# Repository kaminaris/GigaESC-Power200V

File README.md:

# GigaPower200V

Compact 50 × 20 mm non-isolated power-supply module for the modular GigaESC platform, intended for the 200 V version. Provides 12 V, 5 V and 3.3 V rails through a separate output connector.

## Board views

## Hardware

- TL494 PWM controller, IR2181 gate driver and TL431 reference circuitry.
- Two AP63356DV buck regulators for the lower-voltage rails.
- Two 2×10 connectors separating input and output connections.
- Common ground between input and outputs; no galvanic isolation.

## Connector summary

| Connector | Pins | Signal |
|---|---|---|
| J1 input | 3, 5 | VIN |
| J1 input | 17–20 | GND |
| J2 output | 3, 4 | 12 V |
| J2 output | 7, 8 | 5 V |
| J2 output | 11, 12 | 3.3 V |
| J2 output | 1, 2, 5, 6, 9, 10, 13–16, 19, 20 | GND |

Remaining connector pins are unconnected in the schematic. Use the current schematic as the authoritative pinout.

## Project

Open `GigaPower200V.kicad_pro` in KiCad 10. Schematic and layout are in `GigaPower200V.kicad_sch` and `GigaPower200V.kicad_pcb`. Local libraries are included; keep the connector STEP model alongside the project.

The project name describes the intended voltage class, not a measured operating limit. Input range, output loading and thermal performance require hardware validation. The inherited `LM5164_DESIGN.md` describes an earlier design and is not documentation for the current TL494 implementation.

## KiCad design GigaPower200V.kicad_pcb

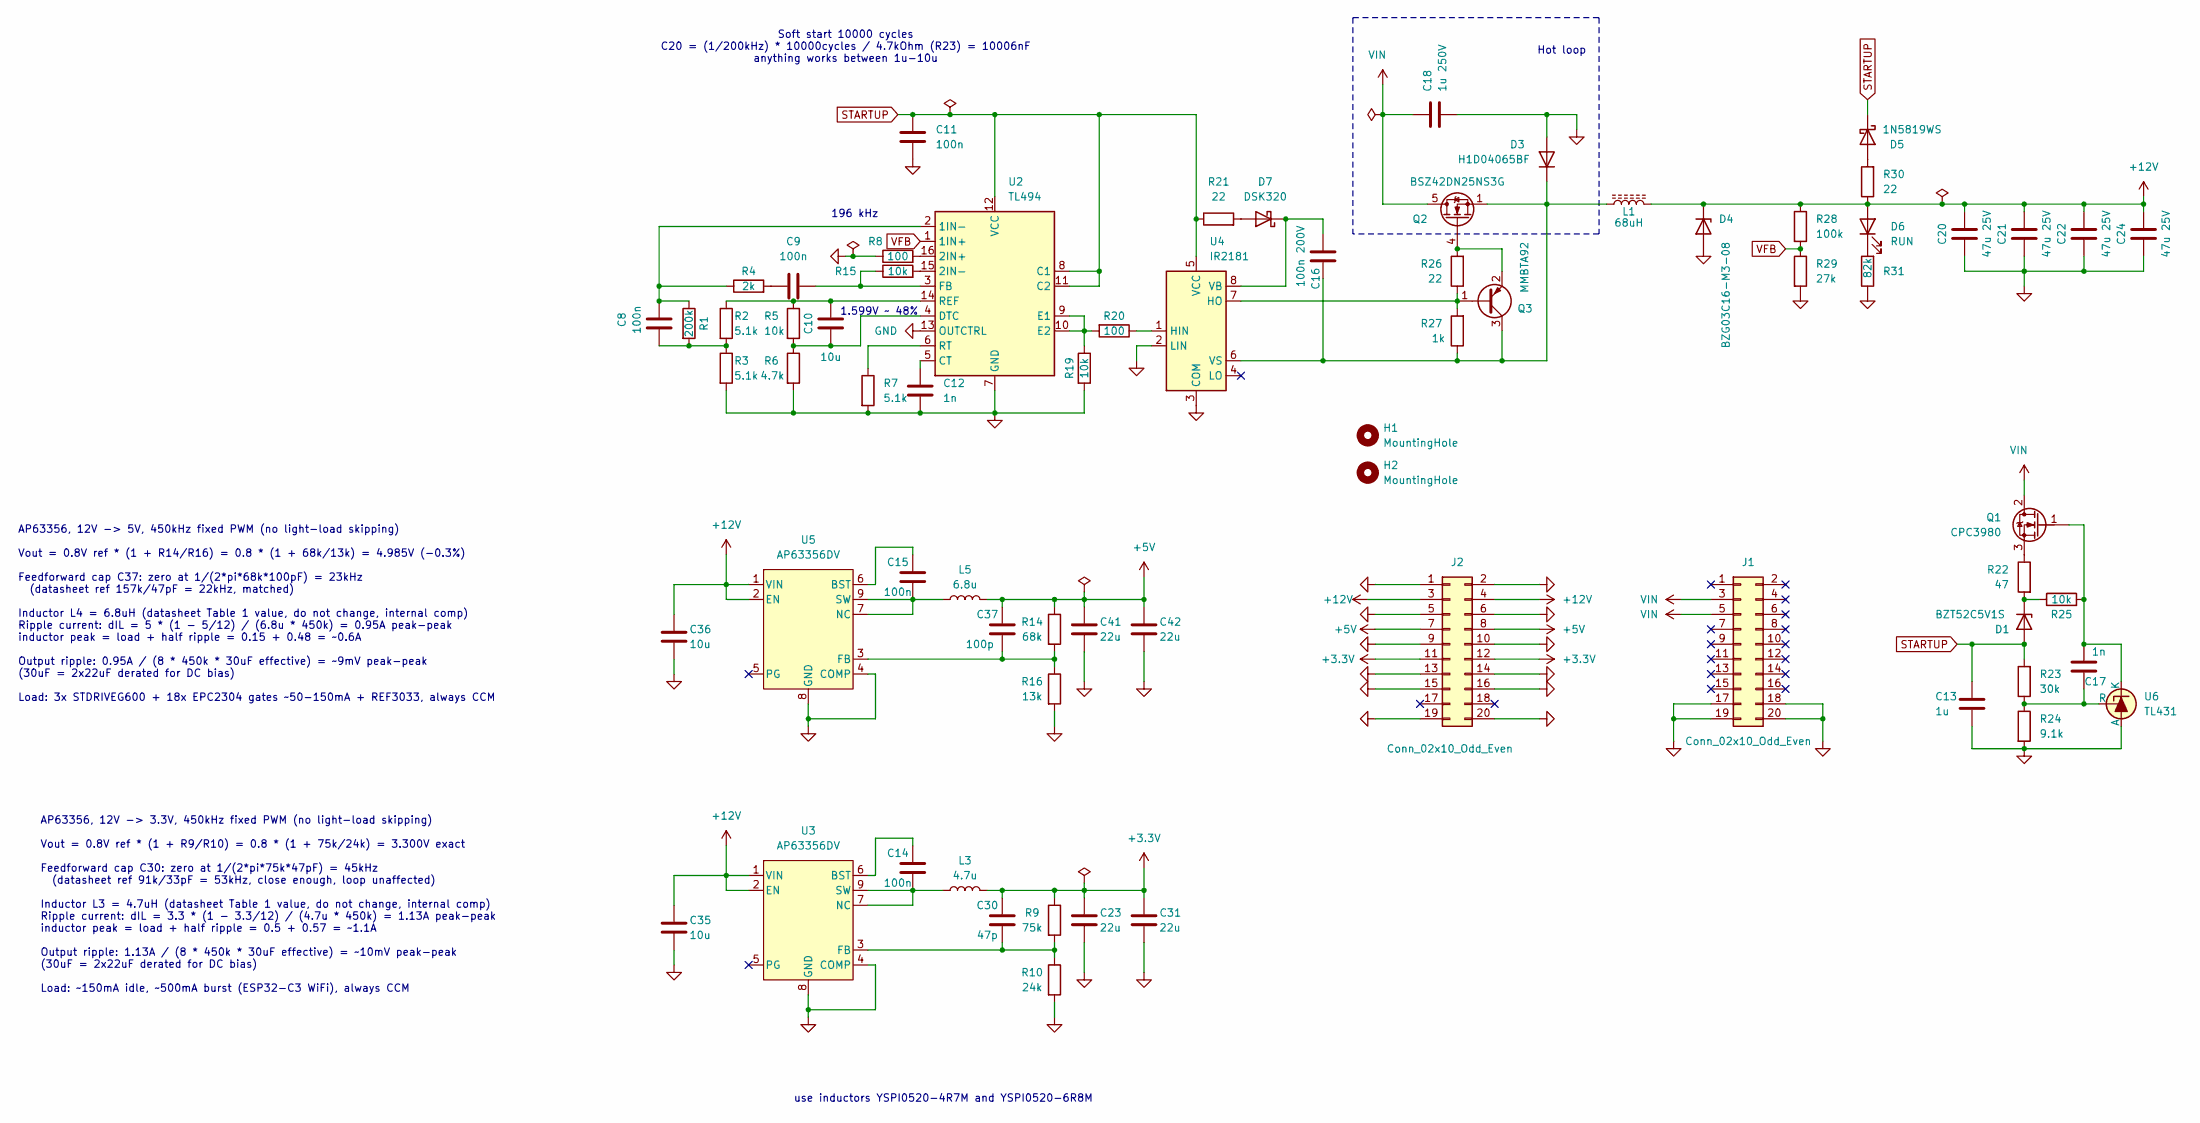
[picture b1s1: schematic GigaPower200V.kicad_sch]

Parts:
C8, C9, C11: 100n; C_0402_1005Metric; MPN C307331; Mouser 581-08055C104KAT4A
C10, C35, C36: 10u; C_0603_1608Metric; MPN C96446
C12, C17: 1n; C_0402_1005Metric; MPN C1523; Mouser 80-C0603C102K5R7081
C13: 1u; C_0402_1005Metric; MPN C52923; Mouser 581-08055C104KAT4A
C14, C15: 100n; C_0603_1608Metric; MPN C14663; Mouser 187-CL21B104KBFNNNE
C16: 100n 200V; C_0805_2012Metric; MPN C784084
C18: 1u 250V; C_1812_4532Metric; MPN C381468
C20, C21, C22, C24: 47u 25V; C_1206_3216Metric; MPN C403725
C23, C31, C41, C42: 22u; C_0603_1608Metric; MPN C86295
C30: 47p; C_0603_1608Metric; MPN C527044; Mouser 187-CL21B104KBFNNNE
C37: 100p; C_0603_1608Metric; MPN C14858; Mouser 187-CL21B104KBFNNNE
D1: BZT52C5V1S; D_SOD-323_HandSoldering; MPN C2886317
D3: H1D04065BF; D_SMB; MPN C52145208
D4: BZG03C16-M3-08; D_SMA; MPN C5224074; Mouser 821-1SMB5928
D5: 1N5819WS; D_SOD-323_HandSoldering; MPN C191023
D6: RUN; D_0603_1608Metric; MPN C2290
D7: DSK320; D_SOD-123; MPN C5290222; Mouser 750-SS520B-HF
H1, H2: MountingHole; MountingHole_3.2mm_M3_DIN965
J1, J2: Conn_02x10_Odd_Even; Hanxia_HX_PM1.0-2x10P_ZC; MPN HX PM1.0-2x10P ZC; LCSC C22465702
L1: 68uH; L_Chilisin_BMRB00060650; MPN C5189964
L3: 4.7u; L_Sunlord_SWPA5040S; MPN C341032; Mouser C341032
L5: 6.8u; L_Sunlord_SWPA5040S; MPN C36411; Mouser C341032
Q1: CPC3980; SOT-223-3_TabPin2; MPN C5373317
Q2: BSZ42DN25NS3G; Diodes_PowerDI3333-8; MPN C6869298
Q3: MMBTA92; SOT-23; MPN C916395
R1: 200k; R_0402_1005Metric; MPN C25764; Mouser 603-RC0805FR-0744K2L
R2, R3, R7: 5.1k; R_0402_1005Metric; MPN C25905; Mouser 603-RC0805FR-0744K2L
R4: 2k; R_0402_1005Metric; MPN C4109; Mouser 603-RC0805FR-0744K2L
R5: 10k; R_0402_1005Metric; MPN C25744
R6: 4.7k; R_0603_1608Metric; MPN C23162
R8: 100; R_0402_1005Metric; MPN C25076; Mouser 603-RC0805FR-0744K2L
R9: 75k; R_0603_1608Metric; MPN C23242
R10: 24k; R_0603_1608Metric; MPN C23352
R14: 68k; R_0603_1608Metric; MPN C23231
R15: 10k; R_0402_1005Metric; MPN C25744; Mouser 603-RC0805FR-0744K2L
R16: 13k; R_0603_1608Metric; MPN C22797
R19, R25: 10k; R_0402_1005Metric; MPN C25744; Mouser 71-CRCW080520R0FKEAC
R20: 100; R_0402_1005Metric; MPN C25076; Mouser 71-CRCW080520R0FKEAC
R21, R26, R30: 22; R_0402_1005Metric; MPN C25092; Mouser 71-CRCW080520R0FKEAC
R22: 47; R_0402_1005Metric; MPN C25118
R23: 30k; R_0402_1005Metric; MPN C25776; Mouser 71-CRCW080520R0FKEAC
R24: 9.1k; R_0402_1005Metric; MPN C25926
R27: 1k; R_0402_1005Metric; MPN C11702; Mouser 71-CRCW080520R0FKEAC
R28: 100k; R_0402_1005Metric; MPN C25741
R29: 27k; R_0402_1005Metric; MPN C25771
R31: 82k; R_0402_1005Metric; MPN C4142; Mouser 603-AC0805JR-0710KL
U2: TL494; TSSOP-16_4.4x5mm_P0.65mm; MPN C163520; JLCRotOffset 0
U3, U5: AP63356DV; V-DFN3020-13_DIO; MPN C2157973
U4: IR2181; SOIC-8_3.9x4.9mm_P1.27mm; MPN C37524; JLCRotOffset 0
U6: TL431; SOT-23; MPN C181103

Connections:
+3.3V: C23.1, C30.2, C31.1, J2.11, J2.12, L3.2, R9.1
+5V: C37.2, C41.1, C42.1, J2.7, J2.8, L5.2, R14.1
+12V: C20.1, C21.1, C22.1, C24.1, C35.1, C36.1, D4.1 (K), D6.2 (A), J2.3, J2.4, L1.2, R28.1, R30.1, U3.1 (VIN), U3.2 (EN), U5.1 (VIN), U5.2 (EN)
GND: C11.2, C12.2, C13.2, C18.2, C20.2, C21.2, C22.2, C23.2, C24.2, C31.2, C35.2, C36.2, C41.2, C42.2, D3.2 (A), D4.2 (A), J1.17, J1.18, J1.19, J1.20, J2.1, J2.2, J2.5, J2.6, J2.9, J2.10, J2.13, J2.14, J2.15, J2.16, J2.19, J2.20, R3.2, R6.2, R7.2, R8.1, R10.2, R16.2, R19.2, R24.2, R29.2, R31.1, U2.7 (GND), U2.13 (OUTCTRL), U3.4 (COMP), U3.8 (GND), U4.2 (LIN), U4.3 (COM), U5.4 (COMP), U5.8 (GND), U6.3 (A)
unnamed: C8.2, R1.2, R2.2, R3.1
unnamed: C9.1, R4.2
unnamed: D1.1 (K), R22.2, R25.1
unnamed: C16.2, D3.1 (K), L1.1, Q2.1 (S), Q2.2 (S), Q2.3 (S), Q3.3 (C), R27.1, U4.6 (VS)
unnamed: D5.2 (A), R30.2
unnamed: D6.1 (K), R31.2
unnamed: D7.2 (A), R21.2
unnamed: C16.1, D7.1 (K), U4.8 (VB)
unnamed: C17.1, Q1.1 (G), R25.2, U6.2 (K)
unnamed: Q1.3 (S), R22.1
unnamed: Q2.4 (G), Q3.2 (E), R26.2
unnamed: Q3.1 (B), R26.1, R27.2, U4.7 (HO)
unnamed: C8.1, R1.1, R4.1, U2.2 (1IN-)
unnamed: R8.2, U2.16 (2IN+)
unnamed: R15.2, U2.15 (2IN-)
unnamed: C12.1, U2.5 (CT)
unnamed: C10.2, R5.2, R6.1, U2.4 (DTC)
unnamed: R19.1, R20.2, U2.9 (E1), U2.10 (E2)
unnamed: C9.2, R15.1, U2.3 (FB)
unnamed: C10.1, R2.1, R5.1, U2.14 (REF)
unnamed: R7.1, U2.6 (RT)
unnamed: C14.2, U3.6 (BST)
unnamed: C30.1, R9.2, R10.1, U3.3 (FB)
unnamed: C14.1, L3.1, U3.7 (NC), U3.9 (SW)
unnamed: R20.1, U4.1 (HIN)
unnamed: C15.2, U5.6 (BST)
unnamed: C37.1, R14.2, R16.1, U5.3 (FB)
unnamed: C15.1, L5.1, U5.7 (NC), U5.9 (SW)
unnamed: C17.2, R23.1, R24.1, U6.1 (R)
STARTUP: C11.1, C13.1, D1.2 (A), D5.1 (K), R21.1, R23.2, U2.8 (C1), U2.11 (C2), U2.12 (VCC), U4.5 (VCC)
VFB: R28.2, R29.1, U2.1 (1IN+)
VIN: C18.1, J1.3, J1.5, Q1.2 (D), Q2.5 (D)

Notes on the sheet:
Hot loop
AP63356, 12V -> 3.3V, 450kHz fixed PWM (no light-load skipping) Vout = 0.8V ref * (1 + R9/R10) = 0.8 * (1 + 75k/24k) = 3.300V exact Feedforward cap C30: zero at 1/(2*pi*75k*47pF) = 45kHz (datasheet ref 91k/33pF = 53kHz, close enough, loop unaffected) Inductor L3 = 4.7uH (datasheet Table 1 value, do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
use inductors YSPI0520-4R7M and YSPI0520-6R8M
196 kHz
AP63356, 12V -> 5V, 450kHz fixed PWM (no light-load skipping) Vout = 0.8V ref * (1 + R14/R16) = 0.8 * (1 + 68k/13k) = 4.985V (-0.3%) Feedforward cap C37: zero at 1/(2*pi*68k*100pF) = 23kHz (datasheet ref 157k/47pF = 22kHz, matched) Inductor L4 = 6.8uH (datasheet Table 1 value, do not change, intern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
1.599V ~ 48%
Soft start 10000 cycles C20 = (1/200kHz) * 10000cycles / 4.7kOhm (R23) = 10006nF anything works between 1u-10u

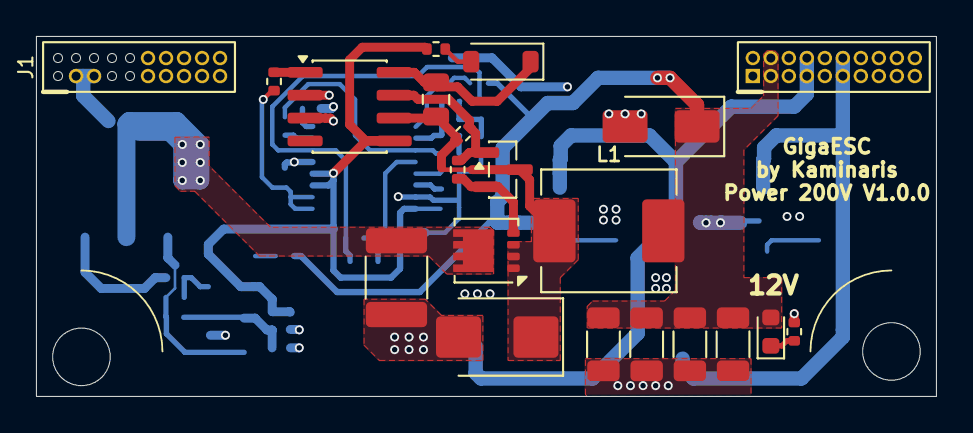
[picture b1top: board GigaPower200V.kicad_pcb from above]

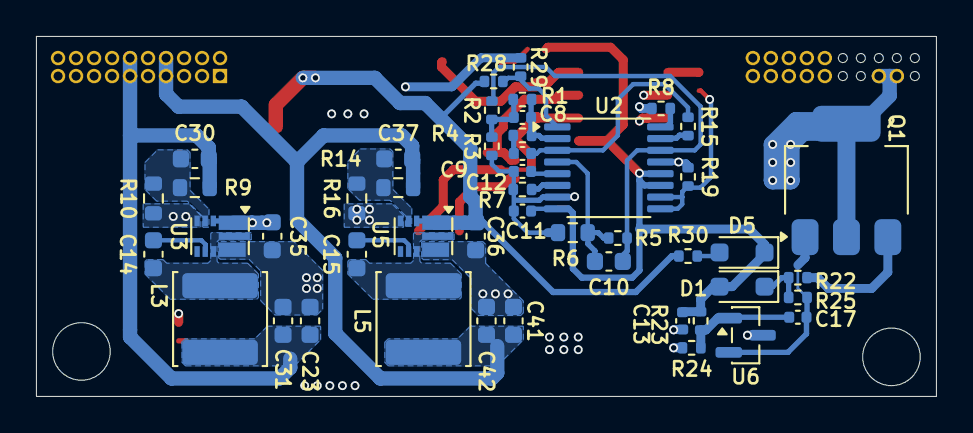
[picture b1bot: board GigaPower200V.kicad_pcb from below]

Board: 4 copper layers, 50.0 x 20.0 mm, 70 parts (47 on the bottom side), 36 nets.
